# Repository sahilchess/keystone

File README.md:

# keystone
a custom mechanical keyboard: cherry mx switches, rp2040?, oled, rgbs and more????

## demo
1. go to https://kicanvas.org/?repo=https%3A%2F%2Fgithub.com%2Fsahilchess%2Fkeystone
2. wait for it to load the repo
3. click on the schematic or pcb file in the sidebar to view it
4. use your mouse to pan and scroll to zoom

## progress

week 2, schematic done, pcb started

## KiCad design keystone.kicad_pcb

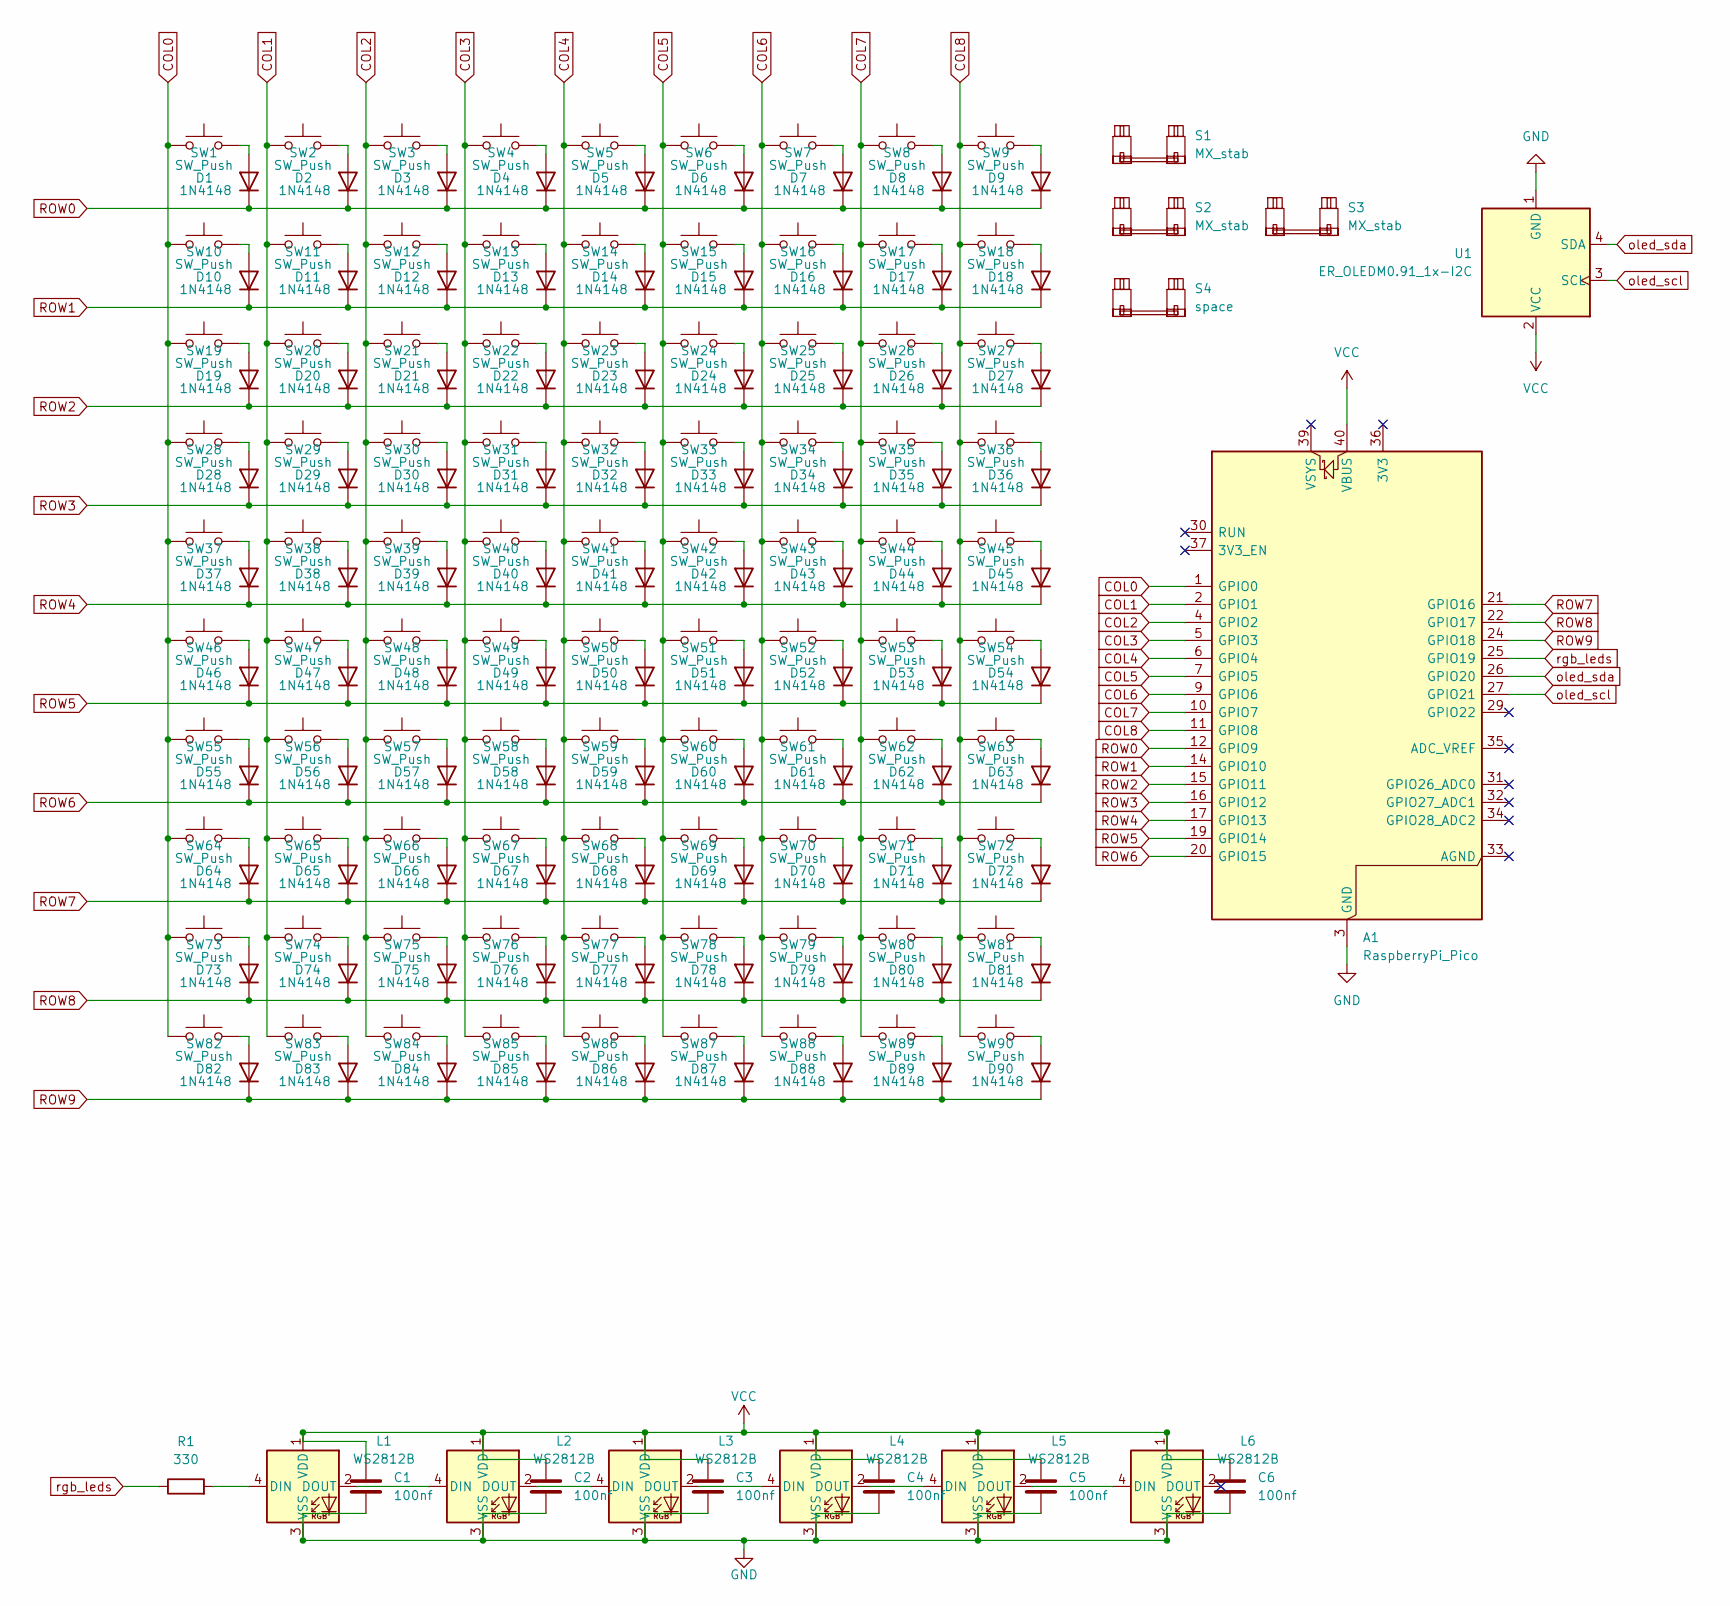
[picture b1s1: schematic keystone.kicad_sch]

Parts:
A1: RaspberryPi_Pico; RaspberryPi_Pico_Common_THT
C1, C2, C3, C4, C5, C6: 100nf; C_0402_1005Metric
D1, D2, D3, D4, D5, D6, D7, D8, D9, D10, D11, D12, D13, D14, D15, D16, D17, D18, D19, D20, D21, D22, D23, D24, D25, D26, D27, D28, D29, D30, D31, D32, D33, D34, D35, D36, D37, D38, D39, D40, D41, D42, D43, D44, D45, D46, D47, D48, D49, D50, D51, D52, D53, D54, D55, D56, D57, D58, D59, D60, D61, D62, D63, D64, D65, D66, D67, D68, D69, D70, D71, D72, D73, D74, D75, D76, D77, D78, D79, D80, D81, D82, D83, D84, D85, D86, D87, D88, D89, D90: 1N4148; D_DO-35_SOD27_P7.62mm_Horizontal
L1, L2, L3, L4, L5, L6: WS2812B; LED_WS2812B_PLCC4_5.0x5.0mm_P3.2mm
R1: 330; R_0402_1005Metric
S1, S2, S3: MX_stab; STAB_MX_2u
S4: space; STAB_MX_6.25u
SW1, SW2, SW3, SW4, SW5, SW6, SW7, SW8, SW9, SW10, SW11, SW12, SW13, SW14, SW15, SW16, SW17, SW18, SW19, SW20, SW21, SW22, SW23, SW24, SW25, SW26, SW27, SW28, SW29, SW30, SW31, SW32, SW33, SW34, SW35, SW36, SW37, SW38, SW39, SW40, SW41, SW42, SW43, SW44, SW45, SW46, SW47, SW48, SW49, SW50, SW51, SW52, SW53, SW54, SW55, SW56, SW57, SW58, SW59, SW60, SW61, SW62, SW63, SW64, SW65, SW66, SW67, SW68, SW69, SW70, SW71, SW72, SW73, SW74, SW75, SW76, SW77, SW78, SW79, SW80, SW81, SW82, SW83, SW84, SW85, SW86, SW87, SW88, SW89, SW90: SW_Push; SW_MX_1u
U1: ER_OLEDM0.91_1x-I2C; SSD1306-0.91-OLED-4pin-128x32

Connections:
COL0: A1.1 (GPIO0), SW1.1, SW10.1, SW19.1, SW28.1, SW37.1, SW46.1, SW55.1, SW64.1, SW73.1, SW82.1
COL1: A1.2 (GPIO1), SW2.1, SW11.1, SW20.1, SW29.1, SW38.1, SW47.1, SW56.1, SW65.1, SW74.1, SW83.1
COL2: A1.4 (GPIO2), SW3.1, SW12.1, SW21.1, SW30.1, SW39.1, SW48.1, SW57.1, SW66.1, SW75.1, SW84.1
COL3: A1.5 (GPIO3), SW4.1, SW13.1, SW22.1, SW31.1, SW40.1, SW49.1, SW58.1, SW67.1, SW76.1, SW85.1
COL4: A1.6 (GPIO4), SW5.1, SW14.1, SW23.1, SW32.1, SW41.1, SW50.1, SW59.1, SW68.1, SW77.1, SW86.1
COL5: A1.7 (GPIO5), SW6.1, SW15.1, SW24.1, SW33.1, SW42.1, SW51.1, SW60.1, SW69.1, SW78.1, SW87.1
COL6: A1.9 (GPIO6), SW7.1, SW16.1, SW25.1, SW34.1, SW43.1, SW52.1, SW61.1, SW70.1, SW79.1, SW88.1
COL7: A1.10 (GPIO7), SW8.1, SW17.1, SW26.1, SW35.1, SW44.1, SW53.1, SW62.1, SW71.1, SW80.1, SW89.1
COL8: A1.11 (GPIO8), SW9.1, SW18.1, SW27.1, SW36.1, SW45.1, SW54.1, SW63.1, SW72.1, SW81.1, SW90.1
GND: A1.3 (GND), A1.8 (GND), A1.13 (GND), A1.18 (GND), A1.23 (GND), A1.28 (GND), A1.38 (GND), C1.2, C2.2, C3.2, C4.2, C5.2, C6.2, L1.3 (VSS), L2.3 (VSS), L3.3 (VSS), L4.3 (VSS), L5.3 (VSS), L6.3 (VSS), U1.1 (GND)
unnamed: D1.2 (A), SW1.2
unnamed: D2.2 (A), SW2.2
unnamed: D3.2 (A), SW3.2
unnamed: D4.2 (A), SW4.2
unnamed: D5.2 (A), SW5.2
unnamed: D6.2 (A), SW6.2
unnamed: D7.2 (A), SW7.2
unnamed: D8.2 (A), SW8.2
unnamed: D9.2 (A), SW9.2
unnamed: D10.2 (A), SW10.2
unnamed: D11.2 (A), SW11.2
unnamed: D12.2 (A), SW12.2
unnamed: D13.2 (A), SW13.2
unnamed: D14.2 (A), SW14.2
unnamed: D15.2 (A), SW15.2
unnamed: D16.2 (A), SW16.2
unnamed: D17.2 (A), SW17.2
unnamed: D18.2 (A), SW18.2
unnamed: D19.2 (A), SW19.2
unnamed: D20.2 (A), SW20.2
unnamed: D21.2 (A), SW21.2
unnamed: D22.2 (A), SW22.2
unnamed: D23.2 (A), SW23.2
unnamed: D24.2 (A), SW24.2
unnamed: D25.2 (A), SW25.2
unnamed: D26.2 (A), SW26.2
unnamed: D27.2 (A), SW27.2
unnamed: D28.2 (A), SW28.2
unnamed: D29.2 (A), SW29.2
unnamed: D30.2 (A), SW30.2
unnamed: D31.2 (A), SW31.2
unnamed: D32.2 (A), SW32.2
unnamed: D33.2 (A), SW33.2
unnamed: D34.2 (A), SW34.2
unnamed: D35.2 (A), SW35.2
unnamed: D36.2 (A), SW36.2
unnamed: D37.2 (A), SW37.2
unnamed: D38.2 (A), SW38.2
unnamed: D39.2 (A), SW39.2
unnamed: D40.2 (A), SW40.2
unnamed: D41.2 (A), SW41.2
unnamed: D42.2 (A), SW42.2
unnamed: D43.2 (A), SW43.2
unnamed: D44.2 (A), SW44.2
unnamed: D45.2 (A), SW45.2
unnamed: D46.2 (A), SW46.2
unnamed: D47.2 (A), SW47.2
unnamed: D48.2 (A), SW48.2
unnamed: D49.2 (A), SW49.2
unnamed: D50.2 (A), SW50.2
unnamed: D51.2 (A), SW51.2
unnamed: D52.2 (A), SW52.2
unnamed: D53.2 (A), SW53.2
unnamed: D54.2 (A), SW54.2
unnamed: D55.2 (A), SW55.2
unnamed: D56.2 (A), SW56.2
unnamed: D57.2 (A), SW57.2
unnamed: D58.2 (A), SW58.2
unnamed: D59.2 (A), SW59.2
unnamed: D60.2 (A), SW60.2
unnamed: D61.2 (A), SW61.2
unnamed: D62.2 (A), SW62.2
unnamed: D63.2 (A), SW63.2
unnamed: D64.2 (A), SW64.2
unnamed: D65.2 (A), SW65.2
unnamed: D66.2 (A), SW66.2
unnamed: D67.2 (A), SW67.2
unnamed: D68.2 (A), SW68.2
unnamed: D69.2 (A), SW69.2
unnamed: D70.2 (A), SW70.2
unnamed: D71.2 (A), SW71.2
unnamed: D72.2 (A), SW72.2
unnamed: D73.2 (A), SW73.2
unnamed: D74.2 (A), SW74.2
unnamed: D75.2 (A), SW75.2
unnamed: D76.2 (A), SW76.2
unnamed: D77.2 (A), SW77.2
unnamed: D78.2 (A), SW78.2
unnamed: D79.2 (A), SW79.2
unnamed: D80.2 (A), SW80.2
unnamed: D81.2 (A), SW81.2
unnamed: D82.2 (A), SW82.2
unnamed: D83.2 (A), SW83.2
unnamed: D84.2 (A), SW84.2
unnamed: D85.2 (A), SW85.2
unnamed: D86.2 (A), SW86.2
unnamed: D87.2 (A), SW87.2
unnamed: D88.2 (A), SW88.2
unnamed: D89.2 (A), SW89.2
unnamed: D90.2 (A), SW90.2
unnamed: L1.4 (DIN), R1.2
unnamed: L1.2 (DOUT), L2.4 (DIN)
unnamed: L2.2 (DOUT), L3.4 (DIN)
unnamed: L3.2 (DOUT), L4.4 (DIN)
unnamed: L4.2 (DOUT), L5.4 (DIN)
unnamed: L5.2 (DOUT), L6.4 (DIN)
ROW0: A1.12 (GPIO9), D1.1 (K), D2.1 (K), D3.1 (K), D4.1 (K), D5.1 (K), D6.1 (K), D7.1 (K), D8.1 (K), D9.1 (K)
ROW1: A1.14 (GPIO10), D10.1 (K), D11.1 (K), D12.1 (K), D13.1 (K), D14.1 (K), D15.1 (K), D16.1 (K), D17.1 (K), D18.1 (K)
ROW2: A1.15 (GPIO11), D19.1 (K), D20.1 (K), D21.1 (K), D22.1 (K), D23.1 (K), D24.1 (K), D25.1 (K), D26.1 (K), D27.1 (K)
ROW3: A1.16 (GPIO12), D28.1 (K), D29.1 (K), D30.1 (K), D31.1 (K), D32.1 (K), D33.1 (K), D34.1 (K), D35.1 (K), D36.1 (K)
ROW4: A1.17 (GPIO13), D37.1 (K), D38.1 (K), D39.1 (K), D40.1 (K), D41.1 (K), D42.1 (K), D43.1 (K), D44.1 (K), D45.1 (K)
ROW5: A1.19 (GPIO14), D46.1 (K), D47.1 (K), D48.1 (K), D49.1 (K), D50.1 (K), D51.1 (K), D52.1 (K), D53.1 (K), D54.1 (K)
ROW6: A1.20 (GPIO15), D55.1 (K), D56.1 (K), D57.1 (K), D58.1 (K), D59.1 (K), D60.1 (K), D61.1 (K), D62.1 (K), D63.1 (K)
ROW7: A1.21 (GPIO16), D64.1 (K), D65.1 (K), D66.1 (K), D67.1 (K), D68.1 (K), D69.1 (K), D70.1 (K), D71.1 (K), D72.1 (K)
ROW8: A1.22 (GPIO17), D73.1 (K), D74.1 (K), D75.1 (K), D76.1 (K), D77.1 (K), D78.1 (K), D79.1 (K), D80.1 (K), D81.1 (K)
ROW9: A1.24 (GPIO18), D82.1 (K), D83.1 (K), D84.1 (K), D85.1 (K), D86.1 (K), D87.1 (K), D88.1 (K), D89.1 (K), D90.1 (K)
VCC: A1.40 (VBUS), C1.1, C2.1, C3.1, C4.1, C5.1, C6.1, L1.1 (VDD), L2.1 (VDD), L3.1 (VDD), L4.1 (VDD), L5.1 (VDD), L6.1 (VDD), U1.2 (VCC)
oled_scl: A1.27 (GPIO21), U1.3 (SCL)
oled_sda: A1.26 (GPIO20), U1.4 (SDA)
rgb_leds: A1.25 (GPIO19), R1.1

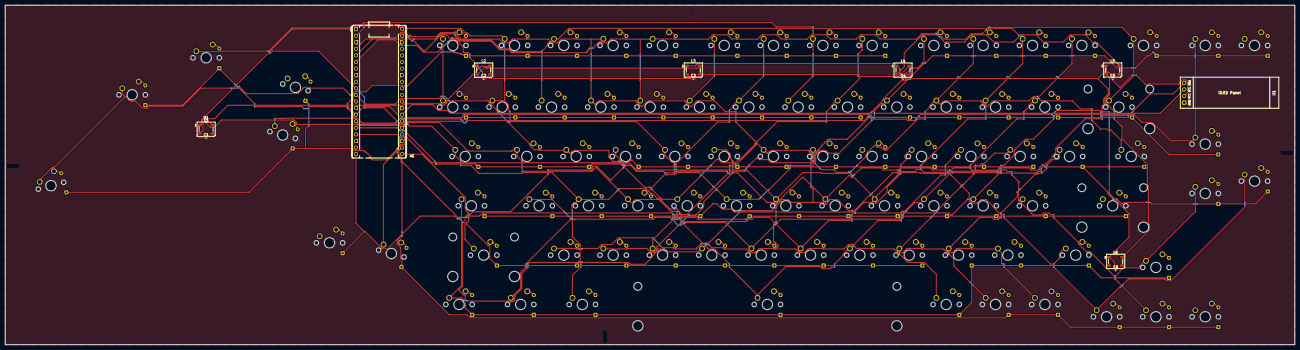
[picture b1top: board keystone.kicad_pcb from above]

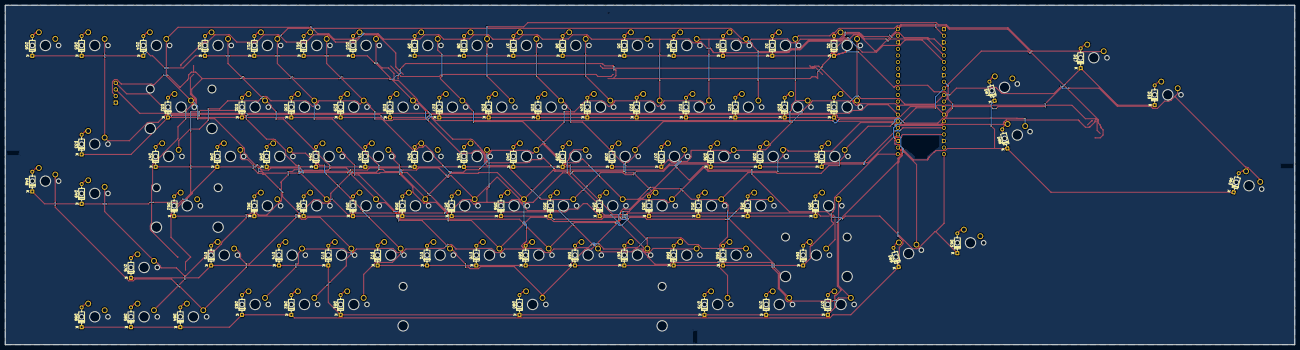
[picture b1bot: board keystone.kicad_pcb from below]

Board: 2 copper layers, 497.9 x 131.1 mm, 199 parts (90 on the bottom side), 120 nets.
